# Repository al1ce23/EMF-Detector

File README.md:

# EMF-Detector
ELECTROMAGNETIC FIELD (EMF) DETECTOR WITH LM358

Original Source: http://www.instructables.com/id/Electromagnetic-Field-EMF-Detector-With-LM358/

Parts List:

* 1x - EMF detector PCB (or you can use perfboard)
* 1x - 9V battery clip (6f22)
* 1x - stereo audio jack 3.5 mm
* 1x - LM358 - or any other pin compatibile dual opamp (TL072 works fine)
* 2x - 100mH radial inductor (may be labeled as 104J)
* 1x - LED (whatever color/parameters)
* 1x - potentiometer 500kΩ stereo linear
* 1x - 1N4148 or any other general purpose diode
* 3x - 1kΩ resistor
* 2x - 10kΩ resistor
* 2x - 100kΩ resistor
* 2x - 100µF electrolytic capacitor (any voltage rating)
* 4x - 2.2µF electrolytic capacitor (any voltage rating)
* 1x - SPDT switch if you want
* 1x - 8 pin socket if you want

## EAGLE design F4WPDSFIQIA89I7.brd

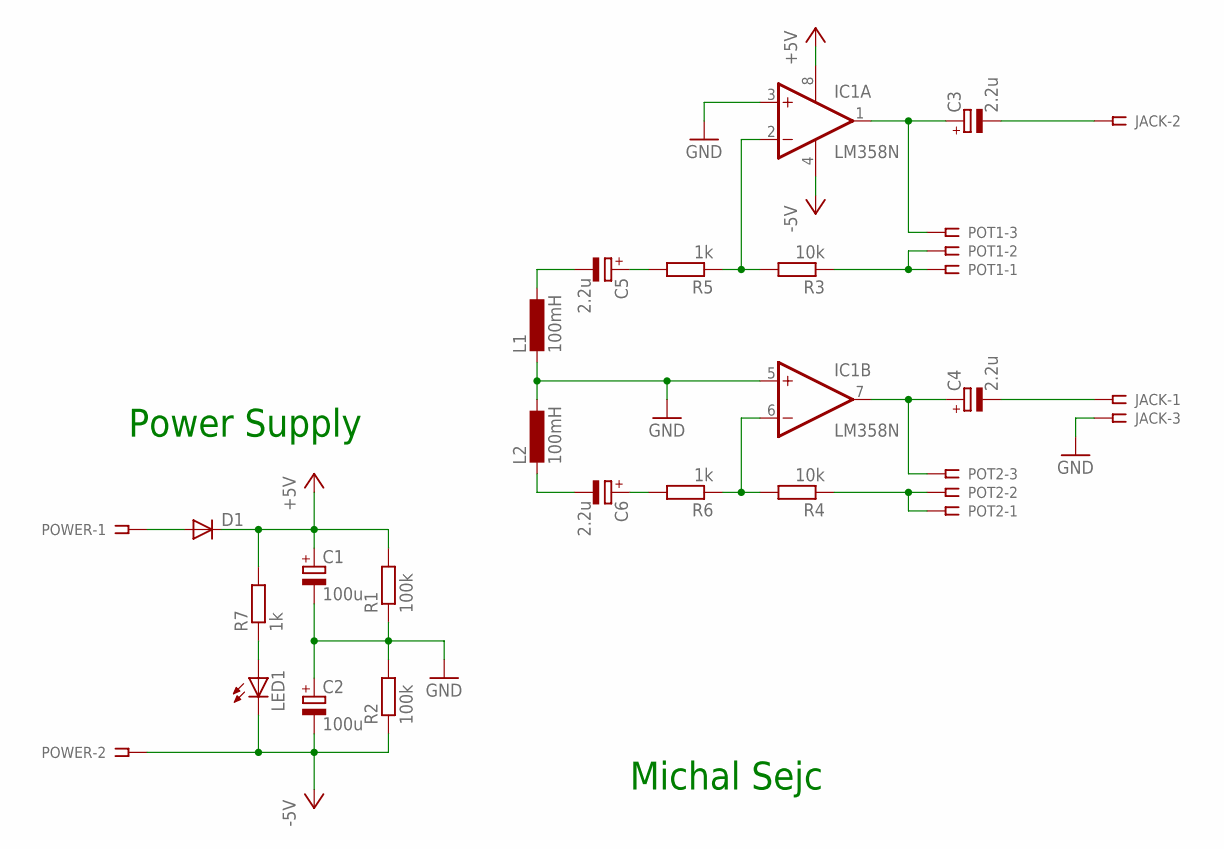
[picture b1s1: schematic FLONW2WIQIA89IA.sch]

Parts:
C1, C2: 100u; E2,5-7
C3, C4, C5, C6: 2.2u; E2,5-6E
D1: 1N4148DO35-7; DO35-7
IC1: LM358N; DIL08
JACK: SSW-103-02-S-S-RA
L1, L2: 100mH; 0204/5
LED1: LED5MM
POT1, POT2: SSW-103-02-S-S-RA
POWER: SSW-102-02-S-S-RA
R1, R2: 100k; 0204/7
R3, R4: 10k; 0204/7
R5, R6, R7: 1k; 0204/7

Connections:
+5V: C1.+, D1.C, IC1.8 (V+), R1.2, R7.2
-5V: C2.-, IC1.4 (V-), LED1.K (C), POWER.2, R2.1
GND: C1.-, C2.+, IC1.3 (+IN), IC1.5 (+IN), JACK.3, L1.2, L2.1, R1.1, R2.2
unnamed: IC1.2 (-IN), R3.2, R5.1
unnamed: C3.+, IC1.1 (OUT), POT1.3
unnamed: C4.+, IC1.7 (OUT), POT2.3
unnamed: POT1.1, POT1.2, R3.1
unnamed: IC1.6 (-IN), R4.2, R6.1
unnamed: POT2.1, POT2.2, R4.1
unnamed: C5.+, R5.2
unnamed: C6.+, R6.2
unnamed: D1.A, POWER.1
unnamed: C3.-, JACK.2
unnamed: C4.-, JACK.1
unnamed: C5.-, L1.1
unnamed: C6.-, L2.2
unnamed: LED1.A, R7.1

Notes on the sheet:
Power Supply
Michal Sejc

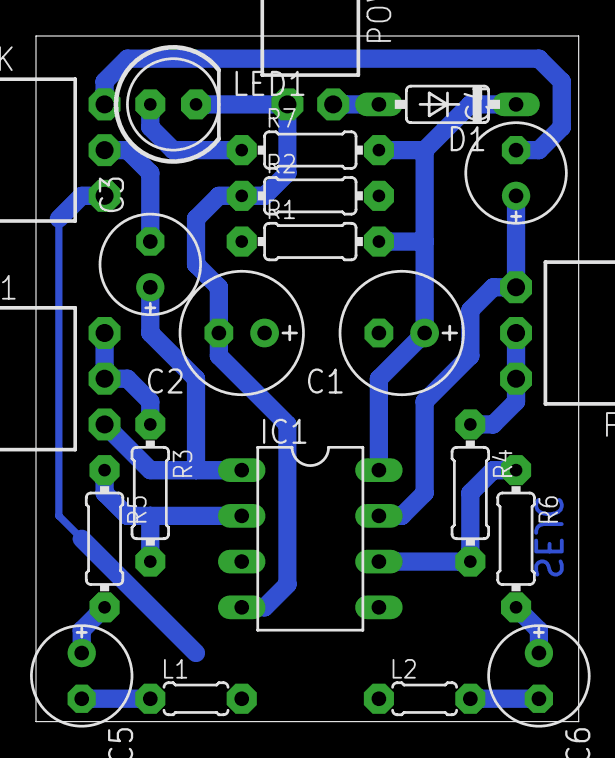
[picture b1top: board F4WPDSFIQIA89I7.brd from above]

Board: 2 copper layers, 30.1 x 38.1 mm, 22 parts (0 on the bottom side), 17 nets.
